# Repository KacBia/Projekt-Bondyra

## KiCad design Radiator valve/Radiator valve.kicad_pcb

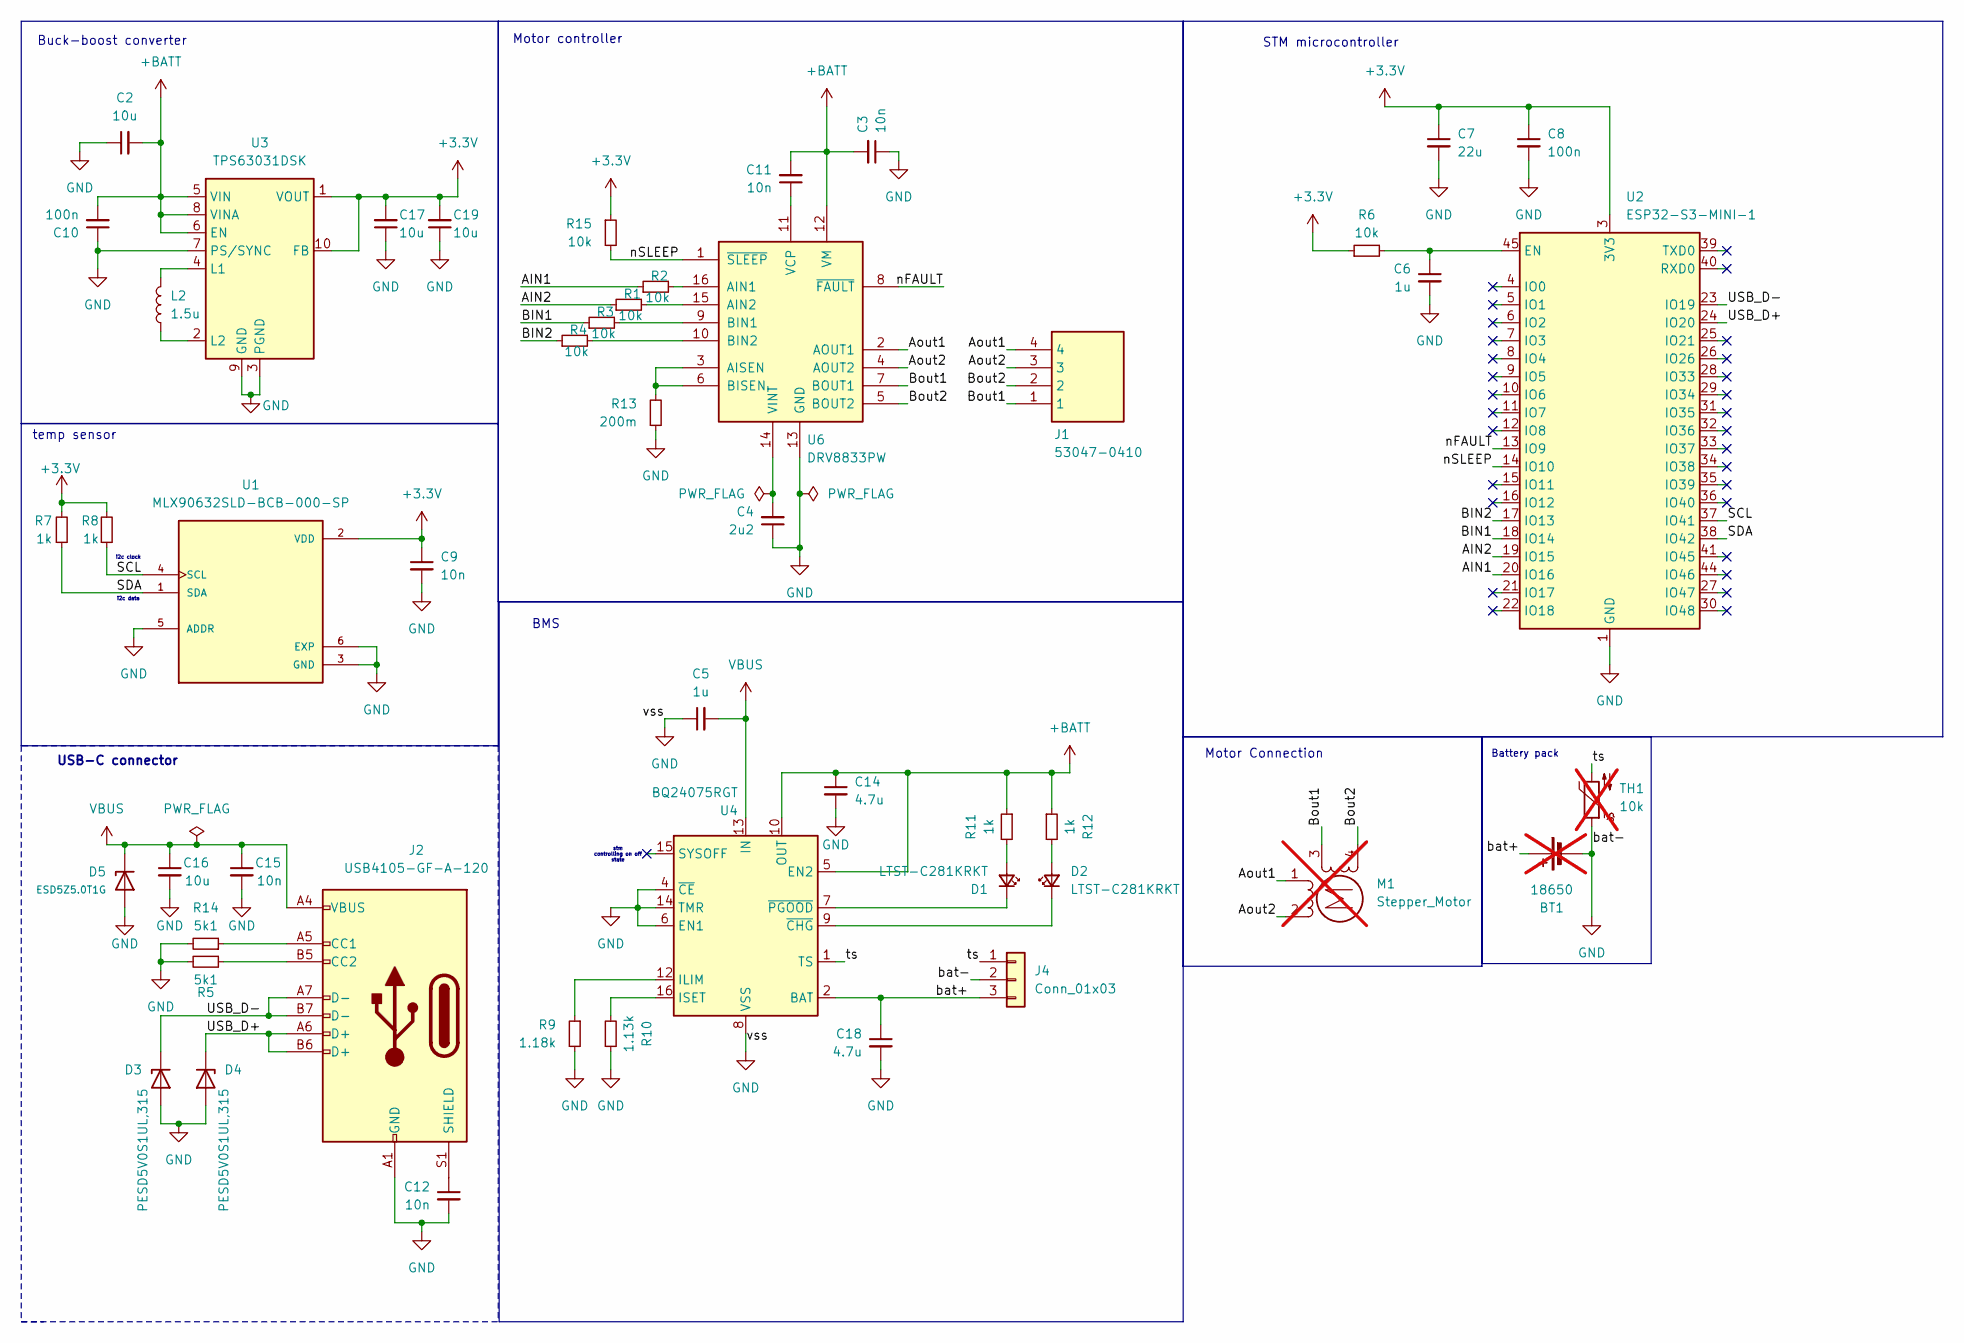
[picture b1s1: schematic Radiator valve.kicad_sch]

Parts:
BT1: 18650; not fitted
C2, C16: 10u; C_0603_1608Metric
C3, C9, C11, C12, C15: 10n; C_0603_1608Metric
C4: 2u2; C_0603_1608Metric
C5: 1u; C_0603_1608Metric
C6: 1u; C_0402_1005Metric
C7: 22u; C_0402_1005Metric
C8, C10: 100n; C_0402_1005Metric
C14, C18: 4.7u; C_0603_1608Metric
C17, C19: 10u; C_0402_1005Metric
D1, D2: LTST-C281KRKT; LED_0402_1005Metric
D3, D4: PESD5V0S1UL,315; D_SOD-523
D5: ESD5Z5.0T1G; D_SOD-523
J1: 53047-0410; Molex_PicoBlade_53047-0410_1x04_P1.25mm_Vertical; Mouser Part Number 538-53047-0410
J2: USB4105-GF-A-120; USB_C_Receptacle_GCT_USB4105-xx-A_16P_TopMnt_Horizontal
J4: Conn_01x03; Molex_PicoBlade_53261-0371_1x03-1MP_P1.25mm_Horizontal
L2: 1.5u; L_Coilcraft_LPS3010
M1: Stepper_Motor; not fitted
R1, R2, R3, R4, R6, R15: 10k; R_0402_1005Metric
R5, R14: 5k1; R_0402_1005Metric
R7, R8, R11, R12: 1k; R_0402_1005Metric
R9: 1.18k; R_0402_1005Metric
R10: 1.13k; R_0402_1005Metric
R13: 200m; R_0402_1005Metric
TH1: 10k; not fitted
U1: MLX90632SLD-BCB-000-SP; IC_MLX90632SLD-BCB-000-SP; PARTREV 12
U2: ESP32-S3-MINI-1; ESP32-S2-MINI-1
U3: TPS63031DSK; WSON-10-1EP_2.5x2.5mm_P0.5mm_EP1.2x2mm
U4: BQ24075RGT; VQFN-16-1EP_3x3mm_P0.5mm_EP1.6x1.6mm
U6: DRV8833PW; TSSOP-16_4.4x5mm_P0.65mm

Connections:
+3.3V: C7.1, C8.1, C9.1, C17.2, C19.2, R6.1, R7.2, R8.2, R15.1, U1.2 (VDD), U2.3 (3V3), U3.1 (VOUT), U3.10 (FB)
+BATT: C2.2, C3.2, C10.2, C11.2, C14.1, R11.1, R12.1, U3.5 (VIN), U3.6 (EN), U3.8 (VINA), U4.5 (EN2), U4.10 (OUT), U4.11 (OUT), U6.12 (VM)
/AIN1: R2.1, U2.20 (IO16)
/AIN2: R1.1, U2.19 (IO15)
/Aout1: J1.4, M1.1, U6.2 (AOUT1)
/Aout2: J1.3, M1.2 (-), U6.4 (AOUT2)
/BIN1: R3.1, U2.18 (IO14)
/BIN2: R4.1, U2.17 (IO13)
/Bout1: J1.1, M1.3, U6.7 (BOUT1)
/Bout2: J1.2, M1.4, U6.5 (BOUT2)
/SCL: R8.1, U1.4 (SCL), U2.37 (IO41)
/SDA: R7.1, U1.1 (SDA), U2.38 (IO42)
/USB_D+: D4.1 (K), J2.A6 (D+), J2.B6 (D+), U2.24 (IO20)
/USB_D-: D3.1 (K), J2.A7 (D-), J2.B7 (D-), U2.23 (IO19)
/bat+: BT1.1 (+), C18.1, J4.3, U4.2 (BAT), U4.3 (BAT)
/nFAULT: U2.13 (IO9), U6.8 (~FAULT)
/nSLEEP: R15.2, U2.14 (IO10), U6.1 (~SLEEP)
/ts: J4.1, TH1.2, U4.1 (TS)
GND: BT1.2 (-), C2.1, C3.1, C4.1, C5.1, C6.2, C7.2, C8.2, C9.2, C10.1, C12.2, C14.2, C15.2, C16.2, C17.1, C18.2, C19.1, D3.2 (A), D4.2 (A), D5.2 (A), J2.A1 (GND), J2.A12 (GND), J2.B1 (GND), J2.B12 (GND), J4.2, R5.2, R9.2, R10.1, R13.1, R14.2, TH1.1, U1.3 (GND), U1.5 (ADDR), U1.6 (EXP), U2.1 (GND), U2.2 (GND), U2.42 (GND), U2.43 (GND), U2.46 (GND), U2.47 (GND), U2.48 (GND), U2.49 (GND), U2.50 (GND), U2.51 (GND), U2.52 (GND), U2.53 (GND), U2.54 (GND), U2.55 (GND), U2.56 (GND), U2.57 (GND), U2.58 (GND), U2.59 (GND), U2.60 (GND), U2.61 (GND), U2.62 (GND), U2.63 (GND), U2.64 (GND), U2.65 (GND), U3.3 (PGND), U3.7 (PS/SYNC), U3.9 (GND), U3.11 (PGND), U4.4 (~CE), U4.6 (EN1), U4.8 (VSS), U4.14 (TMR), U4.17 (VSS), U6.13 (GND)
unnamed: D1.2 (A), R11.2
unnamed: D1.1 (K), U4.7 (~PGOOD)
unnamed: D2.2 (A), R12.2
unnamed: D2.1 (K), U4.9 (~CHG)
unnamed: J2.A5 (CC1), R14.1
unnamed: J2.B5 (CC2), R5.1
unnamed: C12.1, J2.S1 (SHIELD)
unnamed: C6.1, R6.2, U2.45 (EN)
unnamed: L2.2, U3.4 (L1)
unnamed: L2.1, U3.2 (L2)
unnamed: R9.1, U4.12 (ILIM)
unnamed: R10.2, U4.16 (ISET)
unnamed: R2.2, U6.16 (AIN1)
unnamed: R1.2, U6.15 (AIN2)
unnamed: R13.2, U6.3 (AISEN), U6.6 (BISEN)
unnamed: R3.2, U6.9 (BIN1)
unnamed: R4.2, U6.10 (BIN2)
unnamed: C11.1, U6.11 (VCP)
unnamed: C4.2, U6.14 (VINT)
VBUS: C5.2, C15.1, C16.1, D5.1 (K), J2.A4 (VBUS), J2.A9 (VBUS), J2.B4 (VBUS), J2.B9 (VBUS), U4.13 (IN)

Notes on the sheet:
temp sensor
BMS
STM microcontroller
i2c data
Motor Connection
USB-C connector
stm controlling on off state
Motor controller
Battery pack
i2c clock
Buck-boost converter

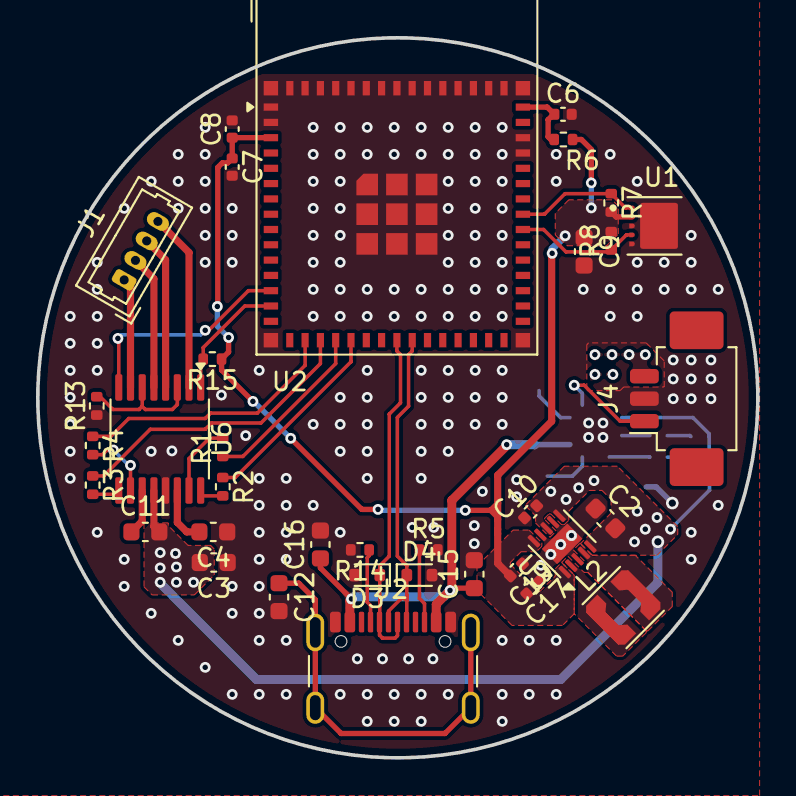
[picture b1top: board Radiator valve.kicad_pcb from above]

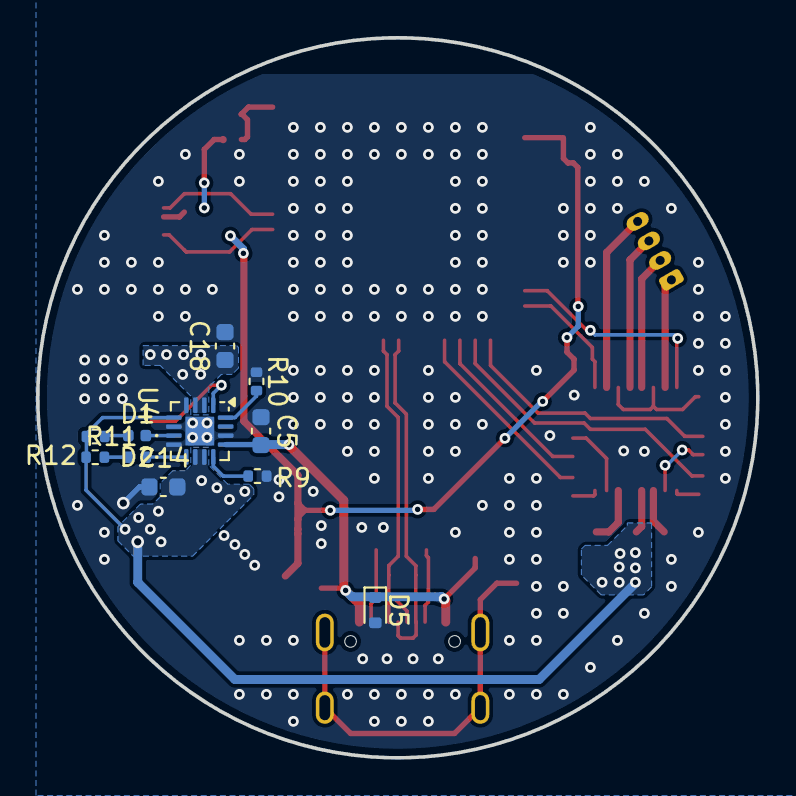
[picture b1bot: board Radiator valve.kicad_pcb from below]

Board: 2 copper layers, 40.0 x 40.0 mm, 46 parts (11 on the bottom side), 39 nets.

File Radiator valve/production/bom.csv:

Designator,Footprint,Quantity,Value,LCSC Part #
"C10, C8",0402,2,100n,
"C11, C12, C15, C3, C9",0603,5,10n,
"C14, C18",0603,2,4.7u,
"C16, C2",0603,2,10u,
"C17, C19",0402,2,10u,
C4,0603,1,2u2,
C5,0603,1,1u,
C6,0402,1,1u,
C7,0402,1,22u,
"D1, D2",0402,2,LTST-C281KRKT,
"D3, D4",D_SOD-523,2,"PESD5V0S1UL,315",
D5,D_SOD-523,1,ESD5Z5.0T1G,
J1,Molex_PicoBlade_53047-0410_1x04_P1.25mm_Vertical,1,53047-0410,
J2,USB_C_Receptacle_GCT_USB4105-xx-A_16P_TopMnt_Horizontal,1,USB4105-GF-A-120,
J4,Molex_PicoBlade_53261-0371_1x03-1MP_P1.25mm_Horizontal,1,Conn_01x03,
L2,L_Coilcraft_LPS3010,1,1.5u,
"R1, R15, R2, R3, R4, R6",0402,6,10k,
R10,0402,1,1.13k,
"R11, R12, R7, R8",0402,4,1k,
R13,0402,1,200m,
"R14, R5",0402,2,5k1,
R9,0402,1,1.18k,
U1,IC_MLX90632SLD-BCB-000-SP,1,MLX90632SLD-BCB-000-SP,
U2,ESP32-S2-MINI-1,1,ESP32-S3-MINI-1,
U3,WSON-10-1EP_2.5x2.5mm_P0.5mm_EP1.2x2mm,1,TPS63031DSK,
U4,VQFN-16-1EP_3x3mm_P0.5mm_EP1.6x1.6mm,1,BQ24075RGT,
U6,TSSOP-16_4.4x5mm_P0.65mm,1,DRV8833PW,

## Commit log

2024-12-11 Moduły
    Dodane główne moduły do schematu
    Do znalezienia BMS (na baterie 3.7v li ion) - bms do ładowania jest, trzeba znaleźć do zarządzania napięciam (undervoltage protection), ma być mały i stosunkowo tani, nie wiem czy coś jeszcze, sprawd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
    Borowiecki
    Pinout mikrokontrolera - co z czym połączyć (datalines, komunikacja do sterownika silnika, do bmsa jeśli trzeba, usbc do programowania i może coś jeszcze)
2024-12-12 Dodany sensor
    i coś jeszcze
2025-01-19 Schematic almost finished
    Still minor fixes to do:
    - check bms (undervoltage protection, ex. voltage divider)
    - battery with pcm
    - figure out how how to make this buck converter work
    - battery and motor connector
2025-01-19 Finished schematic
2025-01-20 Layout started
    Pushed for BOM
2025-01-20 Finished layout
2025-01-20 FInal
2025-01-21 Small changes
